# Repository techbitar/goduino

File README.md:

GOduino III Robot Controller

BACKGROUND

The GOduino III is an Arduino compatible Open Source Hardware robot controller. A while ago, I set out to design a simple robot controller that I can use for both my microcontroller and robotics workshops as well as for my personal tech projects. 

The GOduino III is an Arduino clone. It's built with DIP ICs and through-hole components for ease of assembly and repair.  Also, The GOduino III can be inserted onto a breadboard making it possible to use jumper wires to connect sensors and other parts. The robot controller can handle 2 small servos and 2 DC brushed motors (max 1.2A for each motor).

DESIGNER

Hazim Bitar (techbitar at gmail dot com) 

ORGANIZATION

PIN 13 Protospace (facebook.com/pin13)

DATE

July 12, 2012

CREDIT

Jafar Quttaineh: QA, controller design.
Badr Ghatasheh: QA, variable naming conventions.
Limor Fried: Tutorials and open source products (adafruit.com)

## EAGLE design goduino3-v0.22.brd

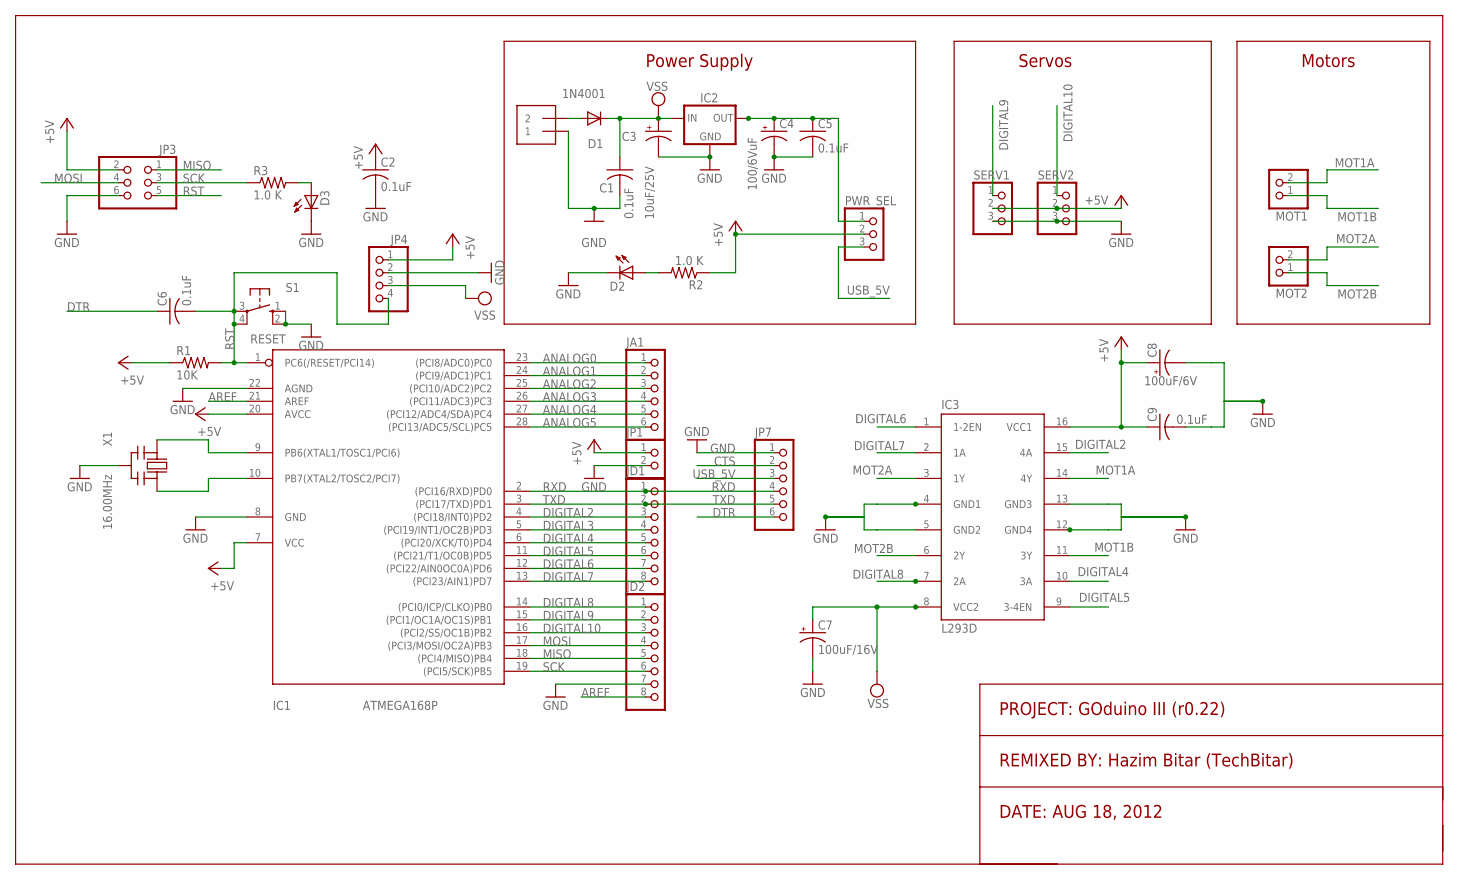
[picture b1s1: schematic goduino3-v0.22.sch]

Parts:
C1, C2, C5, C6, C9: 0.1uF; C025-025X050
C3: 10uF/25V; E2,5-6
C4: 100/6VuF; E2,5-6
C7: 100uF/16V; E2,5-6
C8: 100uF/6V; E2,5-5
D1: 1N4001; DO41-10
D2: LED3MM
D3: Green; LED3MM
IC1: ATMEGA168P; DIL28/3
IC2: 78XXS
IC3: L293D; DIL16
J2: 1X2-3.5MM
JA1: PINHD-1X6CB; 1X06-CLEANBIG
JD1, JD2: PINHD-1X8CLEANBIG; 1X08-CLEANBIG
JP1: PINHD-1X2CB; 1X02-CB
JP3: PINHD-2X3; 2X03
JP4: PINHD-1X4CB; 1X04-CB
JP7: PINHD-1X6CLEAN; 1X06-CLEAN
MOT1, MOT2: PINHD-1X2CB; 1X02-CB
PWR_SEL: PINHD-1X3; 1X03
R1: 10K; 0207/5V
R2, R3: 1.0 K; 0207/5V
S1: RESET; B3F-10XX
SERV1, SERV2: PINHD-1X3; 1X03
X1: 16.00MHz; CERM_OSC

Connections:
+5V: C2.1, C8.+, C9.1, IC1.7 (VCC), IC1.20 (AVCC), IC3.16 (VCC1), JP1.1, JP3.2, JP4.1, PWR_SEL.2, R1.1, R2.1, SERV1.2, SERV2.2
ANALOG0: IC1.23 ((PCI8/ADC0)PC0), JA1.1
ANALOG1: IC1.24 ((PCI9/ADC1)PC1), JA1.2
ANALOG2: IC1.25 ((PCI10/ADC2)PC2), JA1.3
ANALOG3: IC1.26 ((PCI11/ADC3)PC3), JA1.4
ANALOG4: IC1.27 ((PCI12/ADC4/SDA)PC4), JA1.5
ANALOG5: IC1.28 ((PCI13/ADC5/SCL)PC5), JA1.6
AREF: IC1.21 (AREF), JD2.8
CTS: JP7.2
DIGITAL2: IC1.4 ((PCI18/INT0)PD2), IC3.15 (4A), JD1.3
DIGITAL3: IC1.5 ((PCI19/INT1/OC2B)PD3), JD1.4
DIGITAL4: IC1.6 ((PCI20/XCK/T0)PD4), IC3.10 (3A), JD1.5
DIGITAL5: IC1.11 ((PCI21/T1/OC0B)PD5), IC3.9 (3-4EN), JD1.6
DIGITAL6: IC1.12 ((PCI22/AIN0OC0A)PD6), IC3.1 (1-2EN), JD1.7
DIGITAL7: IC1.13 ((PCI23/AIN1)PD7), IC3.2 (1A), JD1.8
DIGITAL8: IC1.14 ((PCI0/ICP/CLKO)PB0), IC3.7 (2A), JD2.1
DIGITAL9: IC1.15 ((PCI1/OC1A/OC1S)PB1), JD2.2, SERV1.1
DIGITAL10: IC1.16 ((PCI2/SS/OC1B)PB2), JD2.3, SERV2.1
DTR: C6.1, JP7.6
GND: C1.2, C2.2, C3.-, C4.-, C5.2, C7.-, C8.-, C9.2, D2.K (C), D3.K (C), IC1.8 (GND), IC1.22 (AGND), IC2.GND, IC3.4 (GND1), IC3.5 (GND2), IC3.12 (GND4), IC3.13 (GND3), J2.1, JD2.7, JP1.2, JP3.6, JP4.2, JP7.1, S1.1 (S), S1.2 (S1), SERV1.3, SERV2.3, X1.P$2 (GND)
MISO: IC1.18 ((PCI4/MISO)PB4), JD2.5, JP3.1
MOSI: IC1.17 ((PCI3/MOSI/OC2A)PB3), JD2.4, JP3.4
MOT1A: IC3.14 (4Y), MOT1.2
MOT1B: IC3.11 (3Y), MOT1.1
MOT2A: IC3.3 (1Y), MOT2.2
MOT2B: IC3.6 (2Y), MOT2.1
unnamed: IC1.9 (PB6(XTAL1/TOSC1/PCI6)), X1.P$1 (IN)
unnamed: IC1.10 (PB7(XTAL2/TOSC2/PCI7)), X1.P$3 (OUT)
unnamed: D2.A, R2.2
unnamed: D3.A, R3.2
unnamed: C4.+, C5.1, IC2.OUT, PWR_SEL.1
RST: C6.2, IC1.1 (PC6(/RESET/PCI14)), JP3.5, JP4.4, R1.2, S1.3, S1.4 (P1)
RXD: IC1.2 ((PCI16/RXD)PD0), JD1.1, JP7.4
SCK: IC1.19 ((PCI5/SCK)PB5), JD2.6, JP3.3, R3.1
TXD: IC1.3 ((PCI17/TXD)PD1), JD1.2, JP7.5
USB_5V: JP7.3, PWR_SEL.3
VSS: C1.1, C3.+, C7.+, D1.A, D1.C, IC2.IN, IC3.8 (VCC2), J2.2, JP4.3

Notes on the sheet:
Power Supply
Servos
Motors
PROJECT: GOduino III (r0.22)
REMIXED BY: Hazim Bitar (TechBitar)
DATE: AUG 18, 2012

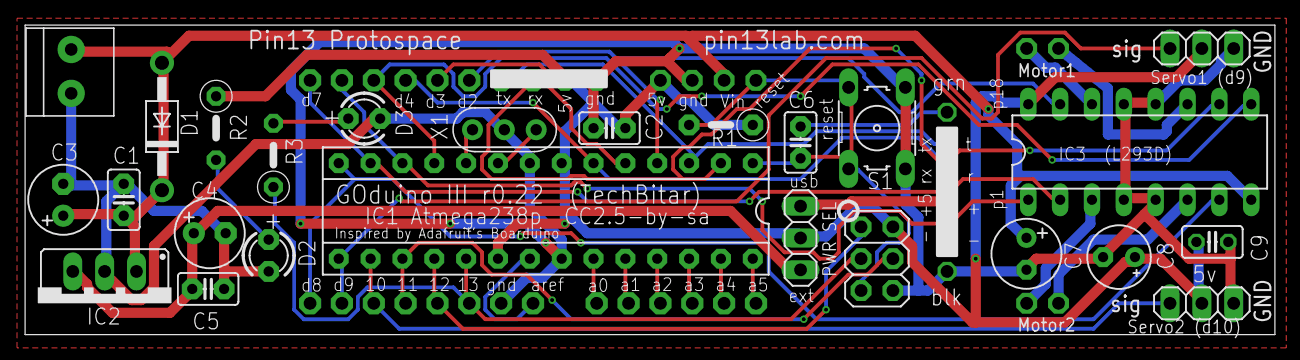
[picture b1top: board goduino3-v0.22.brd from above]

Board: 2 copper layers, 99.7 x 24.7 mm, 33 parts (0 on the bottom side), 36 nets.

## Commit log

2012-08-22 beta versions
2012-08-23 changing naming conventions, dir structure, fix typos
2012-08-23 Merge branch 'master' of https://github.com/techbitar/goduino
    Conflicts:
    README.md
2012-08-23 fixed typos
2012-08-23 typos
2012-08-23 exclude files from CRLF
2012-08-23 add PDF to CRLF exclude
2012-08-23 remove files
2012-08-25 file rename
2012-09-01 updated eagle files
2012-09-01 updated README and created LICENSE files
